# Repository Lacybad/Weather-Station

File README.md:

# Weather Station

This weather station uses an ESP8266 (WeMos D1 Mini), a TFT KMR-1.8 LCD display, a PIR
motion sensor, BJTs and a photoresistor for the display brightness, and an optional 1-wire
temperature sensor (no code for it right now).

This weather station uses darksky for the forecast with a free account. It displays the
current weather temperature, a high and low, and the next two days.

In Settings.h (or MiscSettings.h), add the GPS coordinates, wifi information, and timezone
to make the system work.

This project's PCB was made using JLCPCB. Using the cheapest shipping, it took 6 days to
LAX, a week in customs, and then 3-5 days to a location in the US.

## Icons / Other Code

The icons used for this project are from
[erikflowers](https://github.com/erikflowers/weather-icons).  Using the makefile command
`make imageConvert` converts the images in the folder weather-icons/svg to bmps in a data
folder. This folder can then be uploaded to the ESP8266 using the
[data-uploader](https://github.com/esp8266/arduino-esp8266fs-plugin), which uploads the
data in the /data folder to the SPIFFS file system. It is recommended if using the D1 mini
to have at least 1 MB of storage, and the images take up 124.0 KiB of space.

Other code for this project is from Bodmer's TFT\_eSPI library example for the
[BMP\_functions.ino](https://github.com/Bodmer/TFT_eSPI/blob/master/examples/Generic/TFT_SPIFFS_BMP/BMP_functions.ino),
and converted to work as a C++ library. The modified
[cpp](https://github.com/mwyoung/Weather-Station/blob/master/src/BMP_functions.cpp),
[h](https://github.com/mwyoung/Weather-Station/blob/master/src/BMP_functions.h) and
[license](https://github.com/mwyoung/Weather-Station/blob/master/src/BMP_functions_license.txt)
are in the src directory.

All other libraries (with given versions used) are not really modified from the source
(besides the [TFT\_eSPI v1.4.20](https://github.com/Bodmer/TFT_eSPI) for the pins and
display), and include [ESP8266 Board v2.5.2](https://github.com/esp8266/Arduino) with docs
[ESP8266Wifi and WiFiClientSecure](https://arduino-esp8266.readthedocs.io/en/latest/esp8266wifi/readme.html),
[ArduinoJson v6.13.0](https://github.com/bblanchon/ArduinoJson),
[BearSSL v1.4.0](https://github.com/arduino-libraries/ArduinoBearSSL),
[SPI - ESP8266](https://github.com/esp8266/Arduino/blob/master/libraries/SPI/SPI.h),
[Ticker - ESP8266](https://github.com/esp8266/Arduino/blob/master/libraries/Ticker/src/Ticker.h),
[Timezone v1.2.2](https://github.com/JChristensen/Timezone) and
[TimeLib v1.5.0](https://github.com/PaulStoffregen/Time).

## Data Source
This project originally used DarkSky as a source but moved to
[OpenWeatherMap](https://openweathermap.org/darksky-openweather) after DarkSky shut down
their API. The DarkSky branch in this repo contains the original code that was working
with that API.

## Schematic

For the PCB, the [d1\_mini\_kicad](https://github.com/jerome-labidurie/d1_mini_kicad)
library was used along with the
[digikey-kicad-library](https://github.com/Digi-Key/digikey-kicad-library) and a few
default libraries KiCad for the transistors. The parts can be found in the
[DigiKey purchase list](https://github.com/mwyoung/Weather-Station/blob/master/weatherPCB/DigikeyCartExample.csv),
and this csv file can be uploaded to digikey to buy the parts. Extra parts are included as
backup for buying parts along with buying a large quantity means cost savings. It is also
possible to use a check to save on shipping (could take an extra few days)

Other parts are from Amazon but can be bought on other sites or vendors if it is cheaper.
The parts include a [Wemos d1 mini](https://www.amazon.com/gp/product/B076F53B6S/),
[Photoresistors](https://www.amazon.com/gp/product/B01N0GJ6QP/),
[IR PIR Motion Sensor](https://www.amazon.com/gp/product/B07LF47TRC/),
[LCD Display](https://www.amazon.com/gp/product/B00LSG51MM/),
[Project Boxes](https://www.amazon.com/dp/B07V7X11LJ).

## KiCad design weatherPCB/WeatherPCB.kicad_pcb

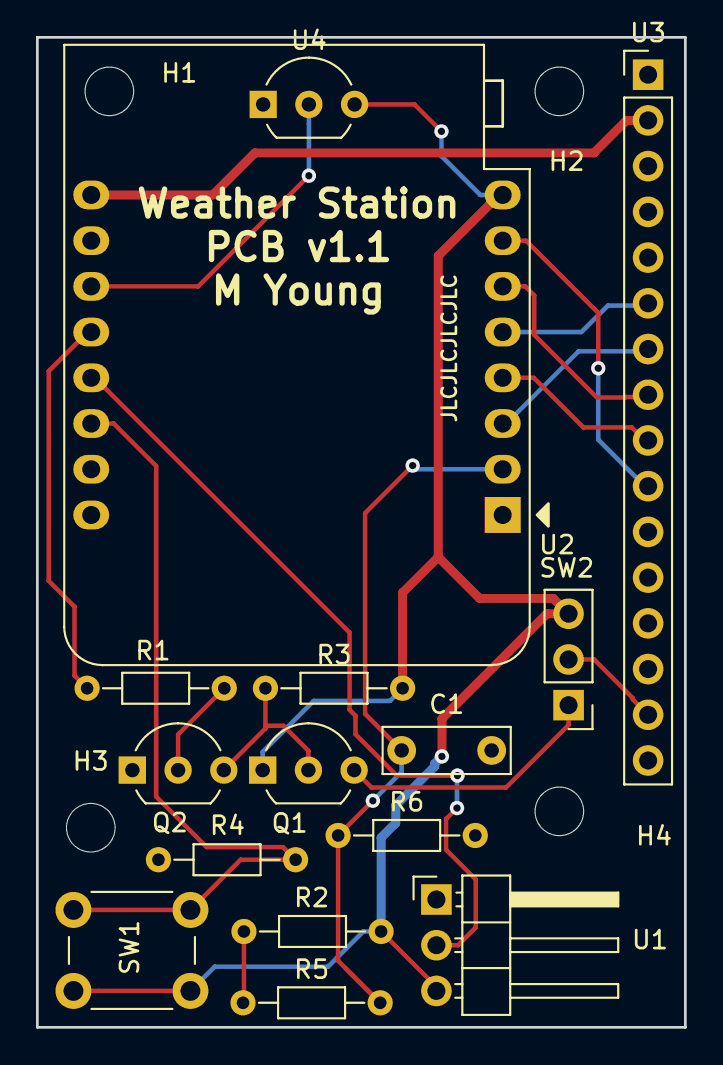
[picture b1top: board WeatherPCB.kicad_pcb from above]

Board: 2 copper layers, 36.0 x 55.0 mm, 19 parts (0 on the bottom side), 18 nets.

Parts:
C1: 0.1u; C_Disc_D7.0mm_W2.5mm_P5.00mm
H1, H2, H3, H4: MountingHole; MountingHole_2.7mm
Q1: 2N4403-ND; TO-92_Inline_Wide
Q2: 2N4401-ND; TO-92_Inline_Wide
R1, R3: 4.7k; R_Axial_DIN0204_L3.6mm_D1.6mm_P7.62mm_Horizontal
R2: 220; R_Axial_DIN0204_L3.6mm_D1.6mm_P7.62mm_Horizontal
R4, R6: 10k; R_Axial_DIN0204_L3.6mm_D1.6mm_P7.62mm_Horizontal
R5: 70-36k; R_Axial_DIN0204_L3.6mm_D1.6mm_P7.62mm_Horizontal
SW1: SW_Push; SW_PUSH_6mm_h5mm
SW2: SW_SPDT; Pin_Header_Straight_1x03_Pitch2.54mm
U1: PIR_MTN_SNR; Pin_Header_Angled_1x03_Pitch2.54mm
U2: WeMos_mini; WEMOS_D1_mini_light
U3: TFTLCD_ST7735R; Pin_Header_Straight_1x16_Pitch2.54mm
U4: DS1822; TO-92_Inline_Wide

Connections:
+3V3: Q1.1, R2.1, R3.2, SW1.1, SW2.3, U1.3, U2.8, U4.3
+5V: U2.9, U3.2
GND: C1.2, Q2.1, R4.2, R6.2, U1.1, U2.10, U3.1, U3.16, U4.1
unnamed: C1.1, R5.2, R6.1, U2.2
unnamed: Q1.2, Q2.3, R3.1
unnamed: Q1.3, SW2.1
unnamed: Q2.2, R1.1
unnamed: R1.2, U2.12
unnamed: R2.2, R5.1
unnamed: R4.1, SW1.2, U2.14
unnamed: SW2.2, U3.15
unnamed: U1.2, U2.13
unnamed: U2.3, U3.7
unnamed: U2.4, U3.9
unnamed: U2.5, U3.6
unnamed: U2.6, U3.8
unnamed: U2.7, U3.10
unnamed: U2.11, U4.2

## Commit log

2019-08-10 Started project, still uses Github API example
2019-08-10 Problems connecting to API
2019-08-13 Now works in insecure mode, code needs to be fixed, removed some comments
2019-08-14 Need different parser/strategy
2019-08-14 Working with ArduinoJson lib
2019-08-15 Working display, code still a mess
2019-08-16 Added makefile converter png to bmp
2019-08-16 bmp now works, added functions
2019-08-16 started testing icons
2019-08-16 most things work besides wind icon
2019-08-17 updated makefile icon generation
2019-08-17 Moved things around, no more strings, can now see svgs, no more spaces
2019-08-18 started on classes
2019-08-19 Updated classes, added sunrise/sunset
2019-08-19 setup some getters, need to refactor to be a single class...
2019-08-19 new setup mostly works, still need to change ArduinoJson conatinsKey
2019-08-19 can now store multiple weather events
2019-08-20 moved some things into functions
2019-08-20 started printing things on display
2019-08-21 Started on time zone stuff, crashes
2019-08-21 No longer crashes
2019-08-21 Time still not working, trying ezTime
2019-08-21 Timezones are messed up - from DarkSky?
2019-08-21 DarkSky uses local time as UTC, no need to convert
2019-08-21 Moving to time.h, outputs in wrong format right now...
2019-08-23 Added tag feature
2019-08-23 Time is 7 hours ahead (UTC), switching to ezTime
2019-08-23 ezTime is off...
2019-08-23 ezTime with OFFSET now is correct, will try smaller libraries with manual timezones
2019-08-23 Timezone.h works, but gives compiler warnings along with not autoupdating...
2019-08-23 Now outputs correctly
2019-08-23 Time is now working, does not autoupdate, but is small
2019-08-23 now outputs some weather
2019-08-23 Started on weather display prototype
2019-08-25 Display kinda works, need to format better
2019-08-27 Edited makefile, started PCB/schematic creation
2019-08-27 Added d1_mini kicad files
2019-08-27 Added display and wiring
2019-08-27 Rename PCB
2019-08-27 Added pin map
2019-08-27 Added display layout temp function
2019-08-27 Added tft display layout
2019-08-27 Removed old tft display layout
2019-08-27 Some graphical issues, displays all information correctly
2019-08-27 Shrink borders
2019-08-28 Updates schematic, changed display output a bit
2019-08-28 more display changes
2019-08-28 compacted serial output, added colors
2019-08-29 Added font height sizes
2019-08-29 Updated some display output, still not perfect
2019-08-29 Fixed humidity, added some color, fixed layout
2019-08-30 Changing default RST pin, adding LTSpice simulation
2019-08-31 Updated schematic for backlighting, renamed pins
2019-08-31 Added photoresistor math, display testing example, updated schematic
2019-08-31 Added timer interrupt for brightness, can now switch between types of brightness control
2019-08-31 Added brightness to main weather project
2019-09-08 Added PIR motion and button test
2019-09-08 Changed display config, different colors, added rgb to hex converter
2019-09-09 Added text colors
2019-09-09 Added PIR and button to schematic
2019-09-09 Added button feature
2019-09-09 Updated printing info
2019-09-09 Working on motion detection
2019-09-09 Motion sensor now works
2019-09-12 Reconfigured BJTs on schematic
2019-09-12 Added debug statements
2019-09-13 Started on PCB
2019-09-16 created pcb
2019-09-17 Rev 1 PCB finished
2019-09-17 Added no motion detection times, now centers some text
2019-09-28 Modified tags, added license
2019-10-07 Ready for Github
2019-10-12 Add simulation info
2019-10-15 Modified PCB for larger resistor sizes and KiCad error with display wiring
2019-10-15 Colors made the temp hard to read
2019-10-15 Added space for optional 1-wire temp sensor
2019-10-16 Trying to fix the n/a icon issue
2019-10-16 Updated humidity/icon generation
2019-10-16 Trying to solve n/a icon mystery
2019-10-16 Finally fixed n/a icon issue, using a work around to store data
2019-10-16 Removed the ptr function
2019-10-17 Cropped svg
2019-10-23 Added comments, brightness now smoother
2019-10-24 Added seconds option for display off
2019-10-24 Fixed bug with motion
2019-10-24 Added code to fix looping bug (hopefully)
2019-10-26 Fixed screen clearing bug
2019-10-28 Fixed turnoff time bug
2019-10-28 Less screen updating
2019-10-28 Fixed issue with hour time/flashing when updating
2019-10-28 Changed brightness scale - now smoother
2019-10-30 Added brightness limit
2019-11-01 Added example location
2019-11-01 Added image
2019-11-01 Moved parts around on schematic, no part changes
2019-11-04 Added root cert check, better motion hour checking, change license
2019-11-04 Add test for ssl cert
2019-11-04 Update test readme
2019-11-05 Changed timing, if data off check GPS coord...
2019-11-05 Update brightness, if analog range is outside range can cause difficulties with wifi connection
2019-11-05 update brightness and motion
2019-11-06 Fixed motion detection
2019-11-17 Moved settings around, updated brightness
2019-11-18 Added daily precipitation amount
2019-11-20 Slight update to brightness variables
2019-11-23 fix https request, add brightness jump
2020-08-22 Update status on project
2020-08-22 Started the process, currently broken on parse FAILED after message
2020-08-23 Mostly working now, need to update icons and a few other things
2020-08-23 Everything is now working
2020-08-23 A few minor layout changes
2020-08-23 Removing timezone remnants, add feels_like approx temp support
2020-08-23 Added more comments, update README with library versions
2020-08-24 Add a bit more color to the display
2020-08-24 Removed ~
2020-08-30 Reverted back to normal temp from approx/feels like as it was 10 deg inaccurate at times
2020-09-12 Updated JSON size, fixed error message output
2020-09-13 Change delay time to a constant
2020-09-15 Update colors and printing word wrap
2020-09-16 Fix precipitation/rain calculation, update blue color function
2020-09-19 Add a bit more space for the rain inches
